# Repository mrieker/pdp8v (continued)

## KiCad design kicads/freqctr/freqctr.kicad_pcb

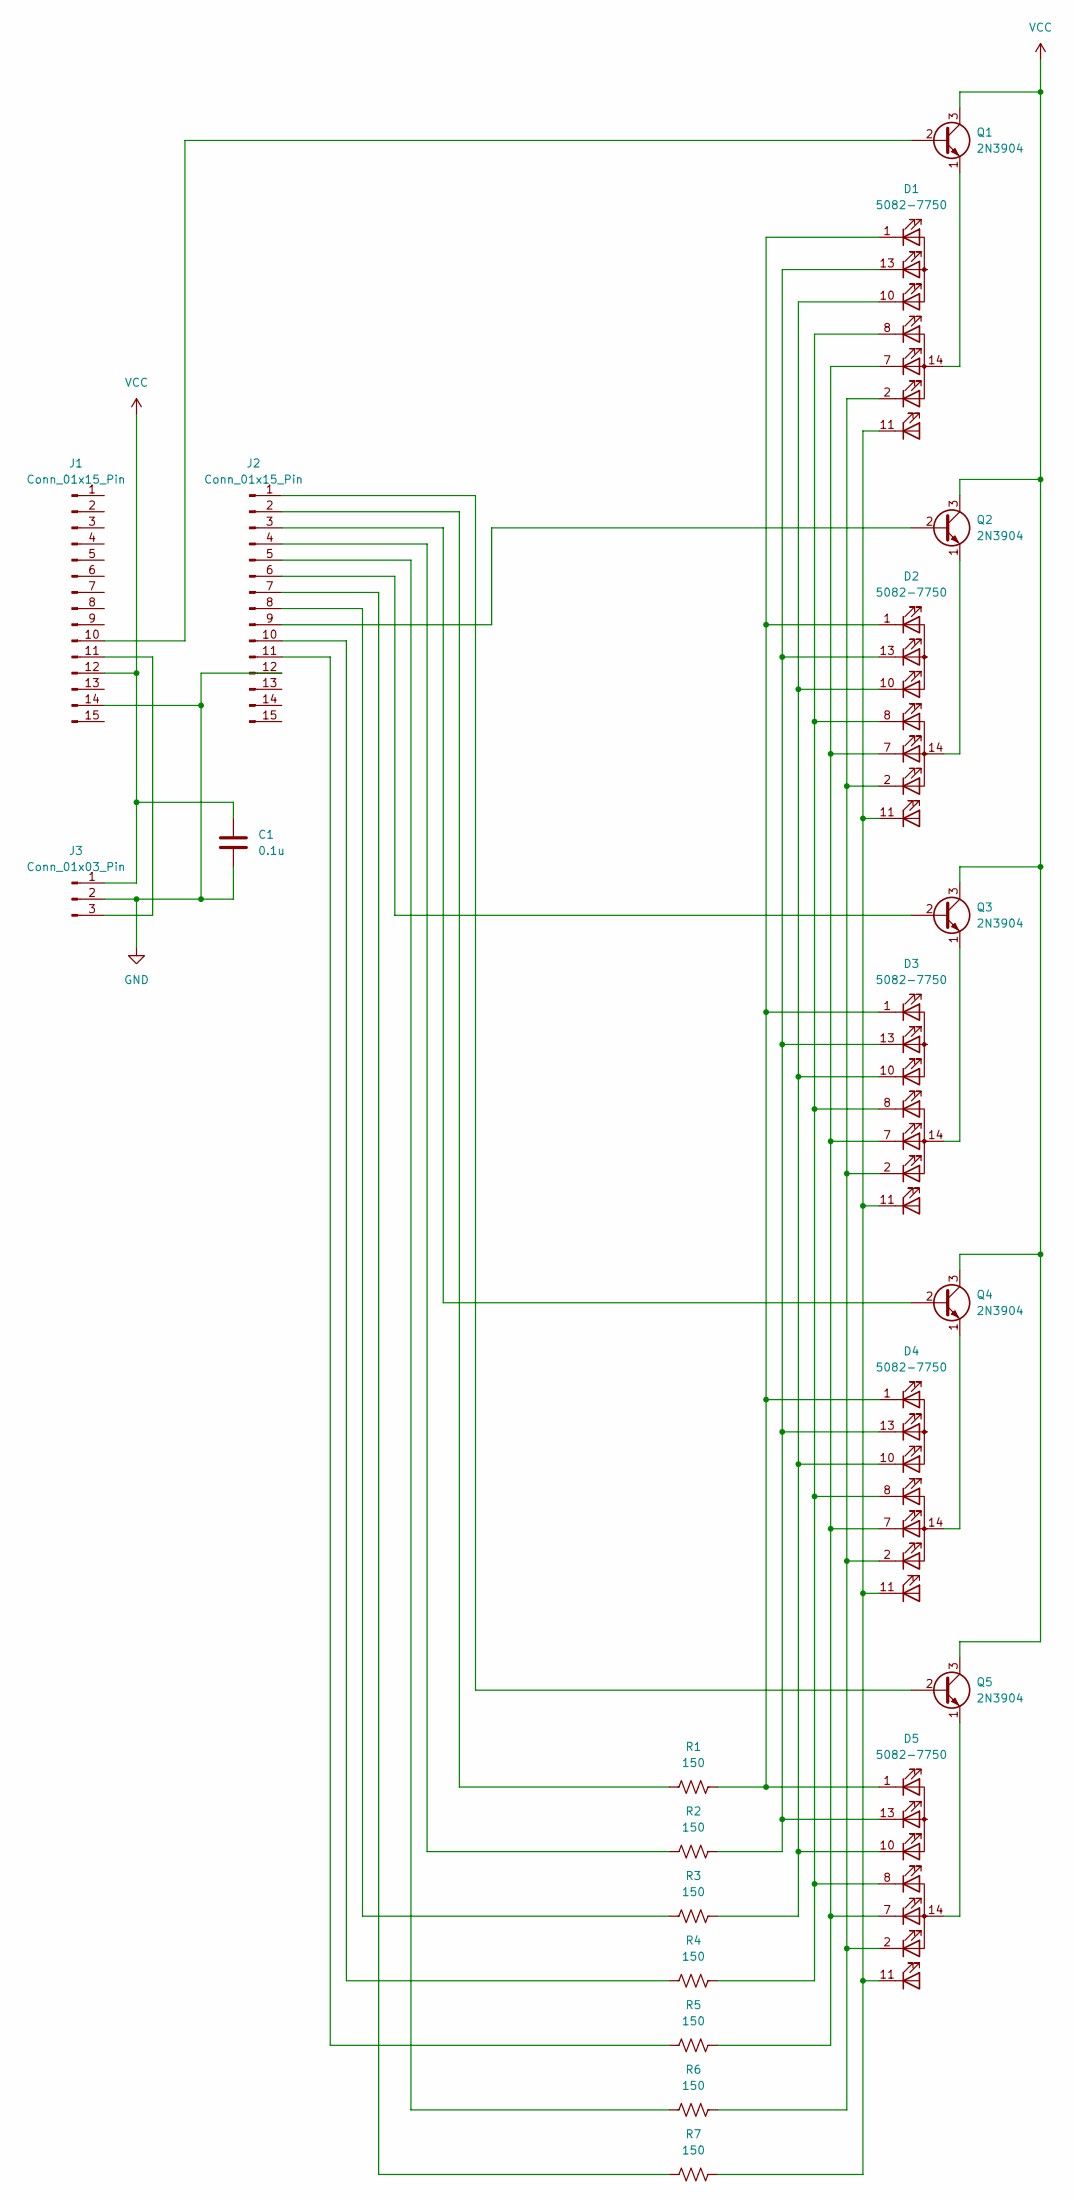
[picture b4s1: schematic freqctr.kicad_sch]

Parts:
C1: 0.1u; C_Axial_L3.8mm_D2.6mm_P7.50mm_Horizontal
D1, D2, D3, D4, D5: 5082-7750; DIP-14_W7.62mm
J1, J2: Conn_01x15_Pin; PinHeader_1x15_P2.54mm_Vertical
J3: Conn_01x03_Pin; PinHeader_1x03_P2.54mm_Vertical
Q1, Q2, Q3, Q4, Q5: 2N3904; TO-92_Inline_Wide
R1, R2, R3, R4, R5, R6, R7: 150; R_Axial_DIN0207_L6.3mm_D2.5mm_P5.08mm_Vertical

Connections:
GND: C1.2, J1.14, J2.12, J3.2
unnamed: D1.1 (a), D2.1 (a), D3.1 (a), D4.1 (a), D5.1 (a), R1.1
unnamed: D1.13 (b), D2.13 (b), D3.13 (b), D4.13 (b), D5.13 (b), R2.1
unnamed: D1.10 (c), D2.10 (c), D3.10 (c), D4.10 (c), D5.10 (c), R3.1
unnamed: D1.8 (d), D2.8 (d), D3.8 (d), D4.8 (d), D5.8 (d), R4.1
unnamed: D1.7 (e), D2.7 (e), D3.7 (e), D4.7 (e), D5.7 (e), R5.1
unnamed: D1.2 (f), D2.2 (f), D3.2 (f), D4.2 (f), D5.2 (f), R6.1
unnamed: D1.11 (g), D2.11 (g), D3.11 (g), D4.11 (g), D5.11 (g), R7.1
unnamed: D1.14 (x), Q1.1 (E)
unnamed: D2.14 (x), Q2.1 (E)
unnamed: D3.14 (x), Q3.1 (E)
unnamed: D4.14 (x), Q4.1 (E)
unnamed: D5.14 (x), Q5.1 (E)
unnamed: J1.10, Q1.2 (B)
unnamed: J1.11, J3.3
unnamed: J2.1, Q5.2 (B)
unnamed: J2.2, R1.2
unnamed: J2.3, Q4.2 (B)
unnamed: J2.4, R2.2
unnamed: J2.5, R6.2
unnamed: J2.6, Q3.2 (B)
unnamed: J2.7, R7.2
unnamed: J2.8, R3.2
unnamed: J2.9, Q2.2 (B)
unnamed: J2.10, R4.2
unnamed: J2.11, R5.2
VCC: C1.1, J1.12, J3.1, Q1.3 (C), Q2.3 (C), Q3.3 (C), Q4.3 (C), Q5.3 (C)

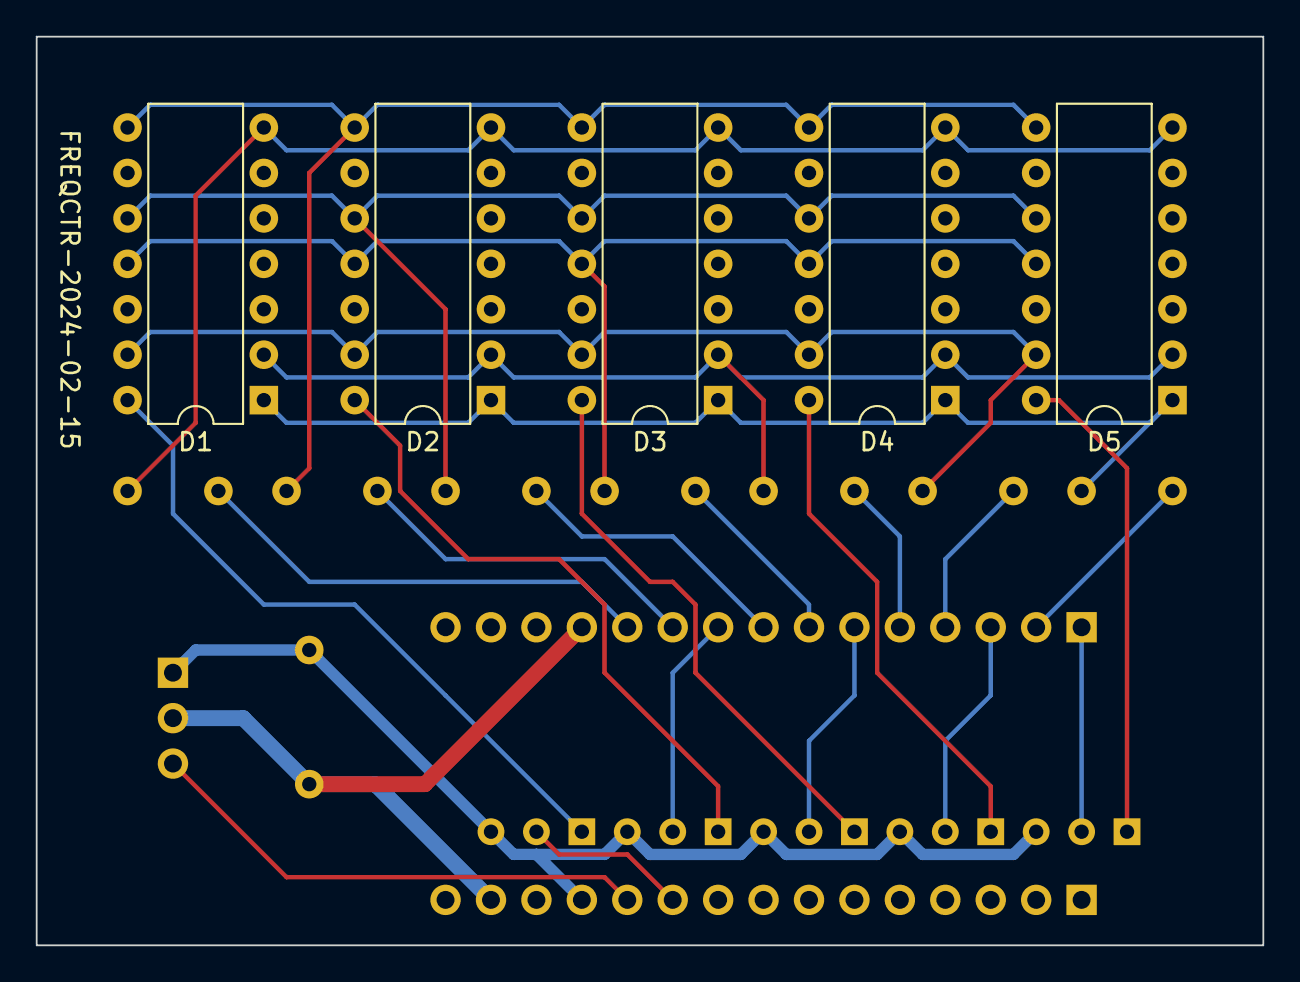
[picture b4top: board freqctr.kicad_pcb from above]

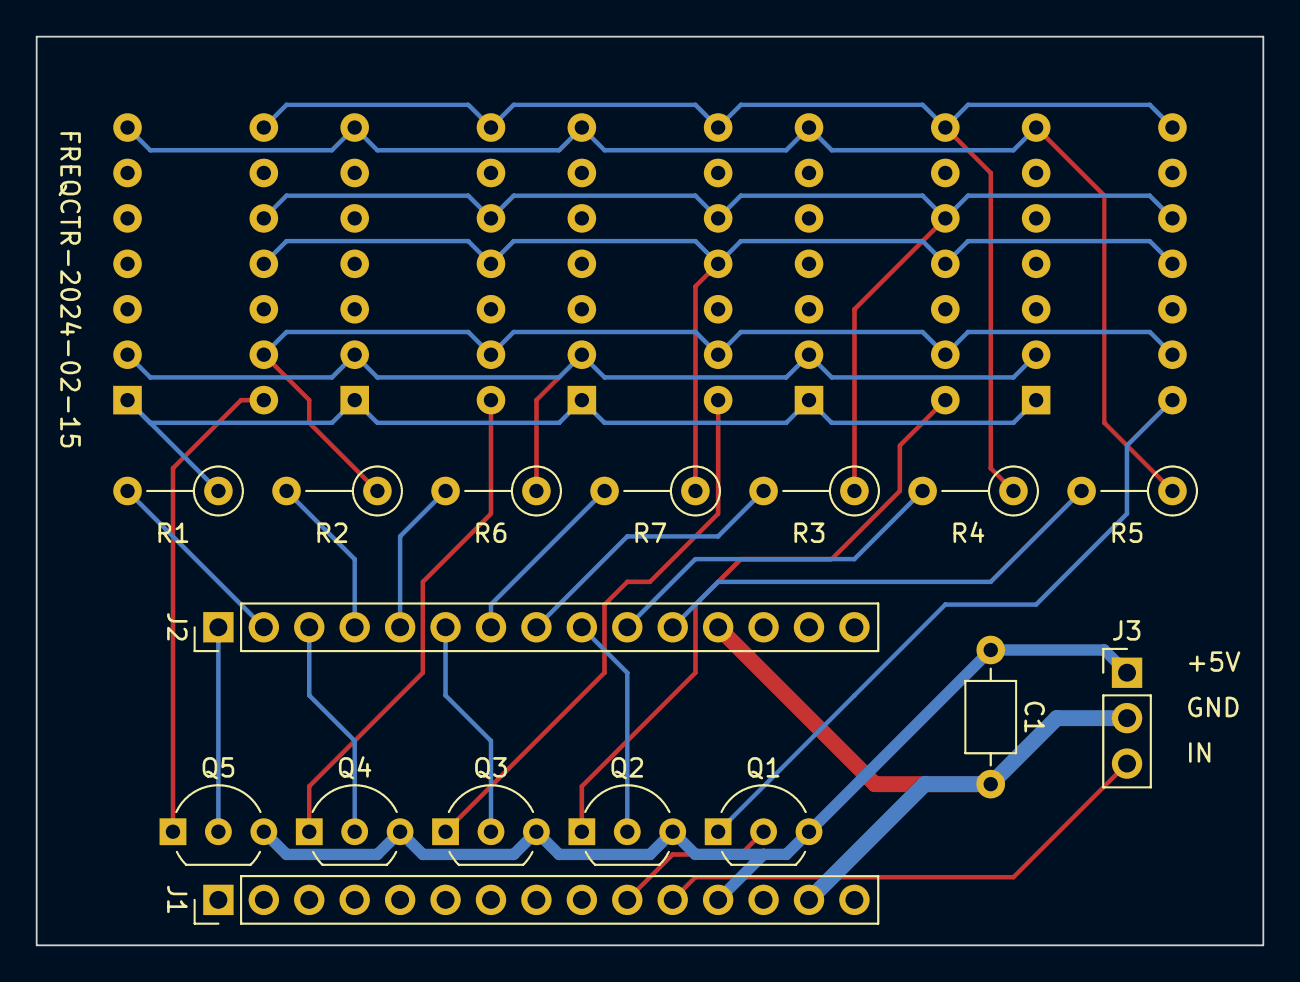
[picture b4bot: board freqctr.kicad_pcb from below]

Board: 2 copper layers, 68.6 x 50.8 mm, 21 parts (16 on the bottom side), 27 nets.

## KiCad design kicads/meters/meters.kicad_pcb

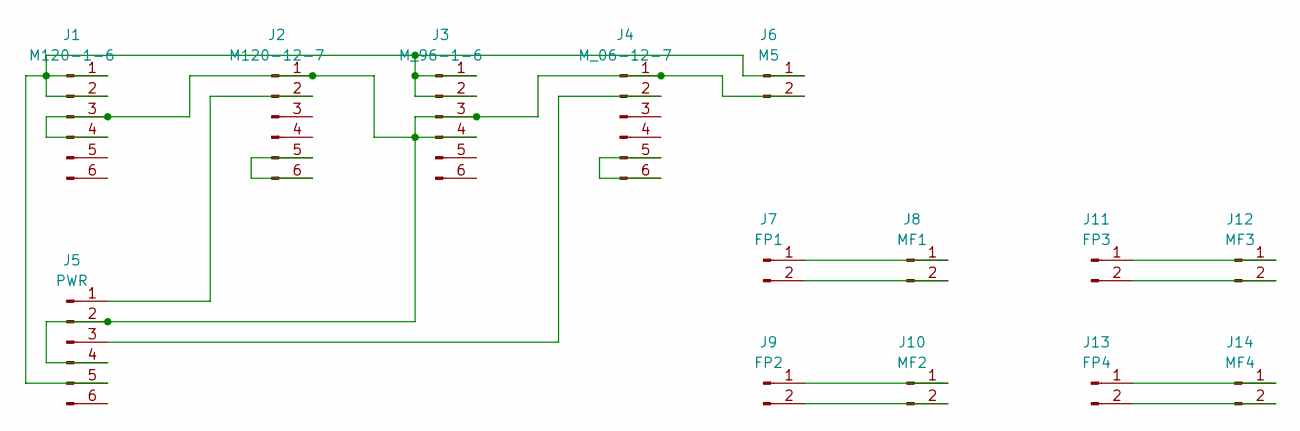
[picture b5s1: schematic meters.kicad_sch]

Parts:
J1: M120-1-6; PinSocket_1x06_P2.54mm_Vertical
J2: M120-12-7; PinSocket_1x06_P2.54mm_Vertical
J3: M_96-1-6; PinSocket_1x06_P2.54mm_Vertical
J4: M_06-12-7; PinSocket_1x06_P2.54mm_Vertical
J5: PWR; PinSocket_1x06_P2.54mm_Vertical
J6: M5; PinSocket_1x02_P2.54mm_Vertical
J7: FP1; PinSocket_1x02_P2.54mm_Vertical
J8: MF1; PinSocket_1x02_P2.54mm_Vertical
J9: FP2; PinSocket_1x02_P2.54mm_Vertical
J10: MF2; PinSocket_1x02_P2.54mm_Vertical
J11: FP3; PinSocket_1x02_P2.54mm_Vertical
J12: MF3; PinSocket_1x02_P2.54mm_Vertical
J13: FP4; PinSocket_1x02_P2.54mm_Vertical
J14: MF4; PinSocket_1x02_P2.54mm_Vertical

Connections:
unnamed: J1.1, J1.2, J3.1, J3.2, J5.5, J6.1
unnamed: J1.3, J1.4, J2.1, J3.3, J3.4, J4.1, J5.2, J5.4, J6.2
unnamed: J2.2, J5.1
unnamed: J2.5, J2.6
unnamed: J4.2, J5.3
unnamed: J4.5, J4.6
unnamed: J7.1, J8.1
unnamed: J7.2, J8.2
unnamed: J9.1, J10.1
unnamed: J9.2, J10.2
unnamed: J11.1, J12.1
unnamed: J11.2, J12.2
unnamed: J13.1, J14.1
unnamed: J13.2, J14.2

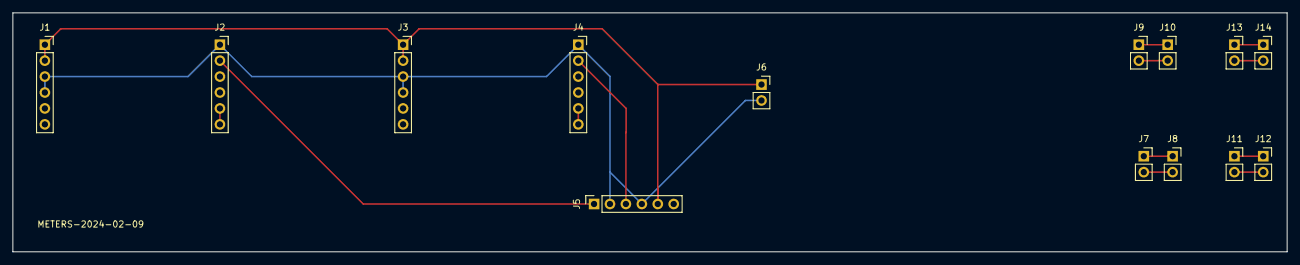
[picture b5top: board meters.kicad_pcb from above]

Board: 2 copper layers, 203.2 x 38.1 mm, 14 parts (0 on the bottom side), 14 nets.

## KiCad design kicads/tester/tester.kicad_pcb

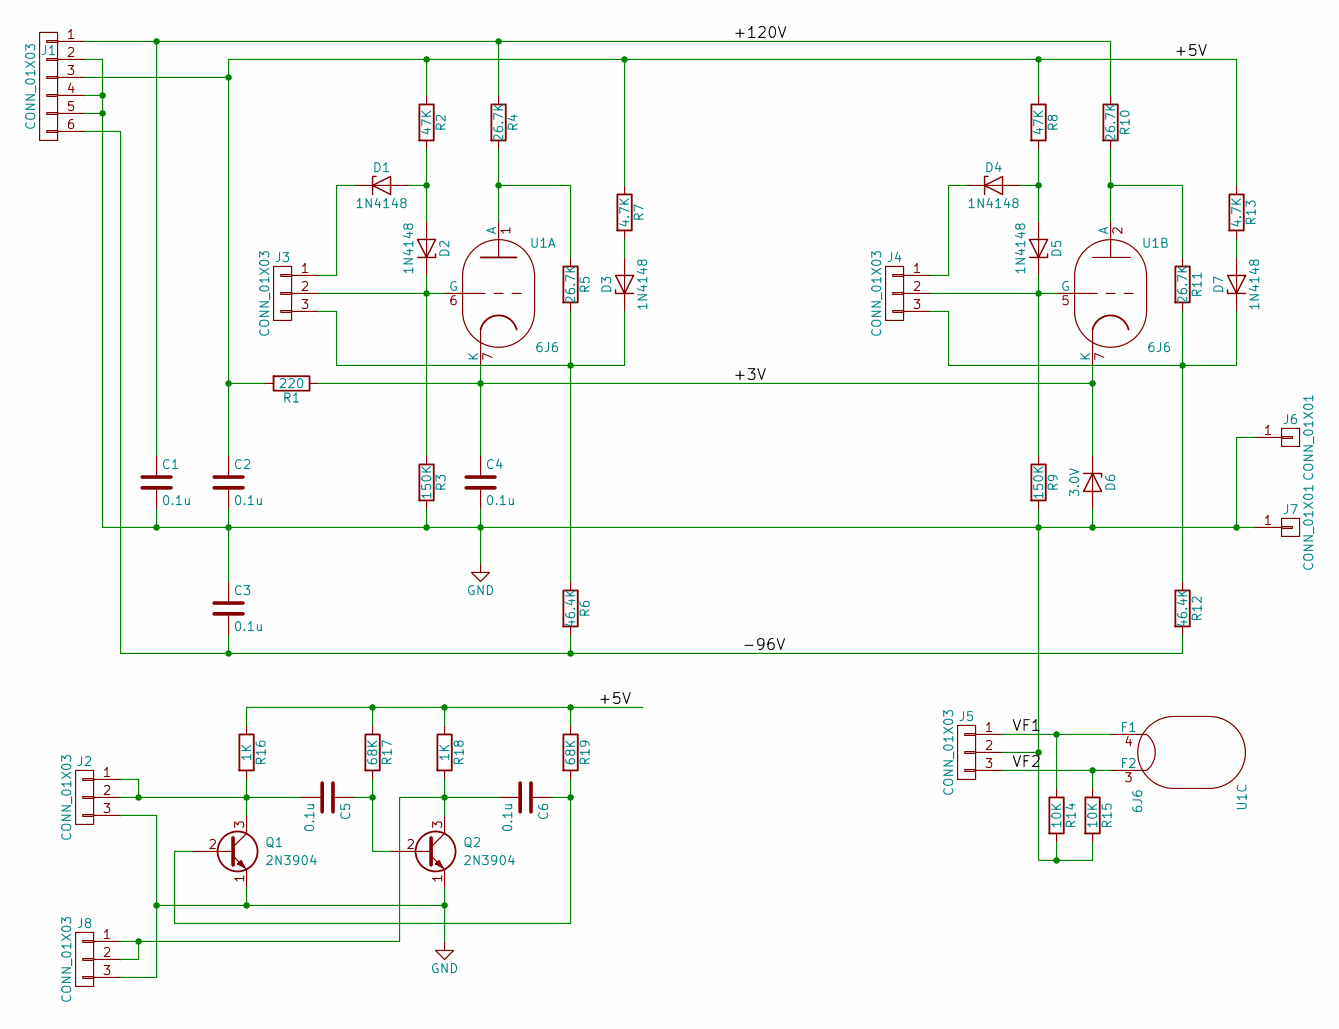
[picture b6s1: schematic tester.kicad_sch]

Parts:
C1, C2, C3, C4, C5, C6: 0.1u; C_Axial_0.1uF
D1, D2, D3, D4, D5, D7: 1N4148; D_DO-35_SOD27_P7.62mm_Horizontal
D6: 3.0V; D_DO-35_SOD27_P7.62mm_Horizontal
J1: CONN_01X03; Pin_Header_Straight_1x06_Pitch2.54mm
J2, J3, J4, J5, J8: CONN_01X03; Pin_Header_Straight_1x03_Pitch2.54mm
J6, J7: CONN_01X01; Pin_Header_Straight_1x01_Pitch2.54mm
Q1, Q2: 2N3904; TO-92_Molded_Wide
R1: 220; R_Axial_QtrWatt
R2, R8: 47K; R_Axial_QtrWatt
R3, R9: 150K; R_Axial_QtrWatt
R4, R5, R10, R11: 26.7K; R_Axial_QtrWatt
R6, R12: 46.4K; R_Axial_QtrWatt
R7, R13: 4.7K; R_Axial_QtrWatt
R14, R15: 10K; R_Axial_QtrWatt
R16, R18: 1K; R_Axial_QtrWatt
R17, R19: 68K; R_Axial_QtrWatt
U1: 6J6; B7G-0.7dia

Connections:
/+3V: C4.1, D6.1 (K), R1.1, U1.7 (K)
/+5V: C2.1, J1.3, R1.2, R2.1, R7.1, R8.1, R13.1, R16.1, R17.1, R18.1, R19.1
/+120V: C1.1, J1.1, R4.1, R10.1
/-96V: C3.2, J1.6, R6.2, R12.2
/VF1: J5.1, R14.1, U1.4 (F1)
/VF2: J5.3, R15.1, U1.3 (F2)
unnamed: C5.1, Q2.2 (B), R17.2
unnamed: C5.2, J2.1, J2.2, Q1.3 (C), R16.2
unnamed: C6.1, Q1.2 (B), R19.2
unnamed: C6.2, J8.1, J8.2, Q2.3 (C), R18.2
unnamed: D1.1 (K), J3.1
unnamed: D1.2 (A), D2.2 (A), R2.2
unnamed: D2.1 (K), J3.2, R3.1, U1.6 (G)
unnamed: D3.1 (K), J3.3, R5.2, R6.1
unnamed: D3.2 (A), R7.2
unnamed: D4.1 (K), J4.1
unnamed: D4.2 (A), D5.2 (A), R8.2
unnamed: D5.1 (K), J4.2, R9.1, U1.5 (G)
unnamed: D7.1 (K), J4.3, R11.2, R12.1
unnamed: D7.2 (A), R13.2
unnamed: R4.2, R5.1, U1.1 (A)
unnamed: R10.2, R11.1, U1.2 (A)

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
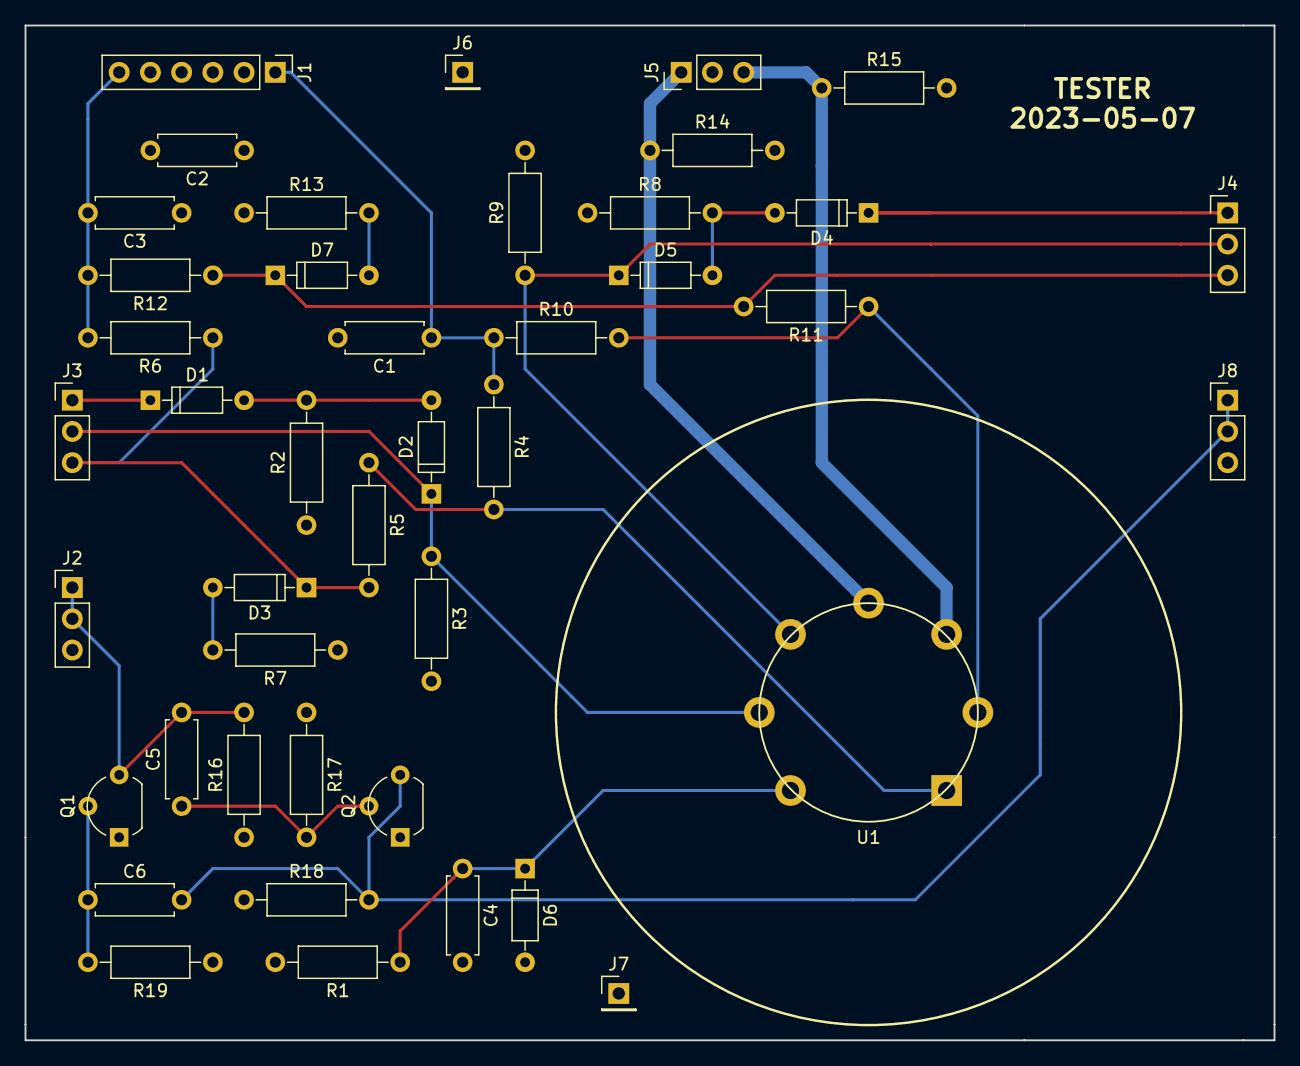
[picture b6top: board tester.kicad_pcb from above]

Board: 4 copper layers, 101.6 x 82.5 mm, 43 parts (0 on the bottom side), 23 nets.

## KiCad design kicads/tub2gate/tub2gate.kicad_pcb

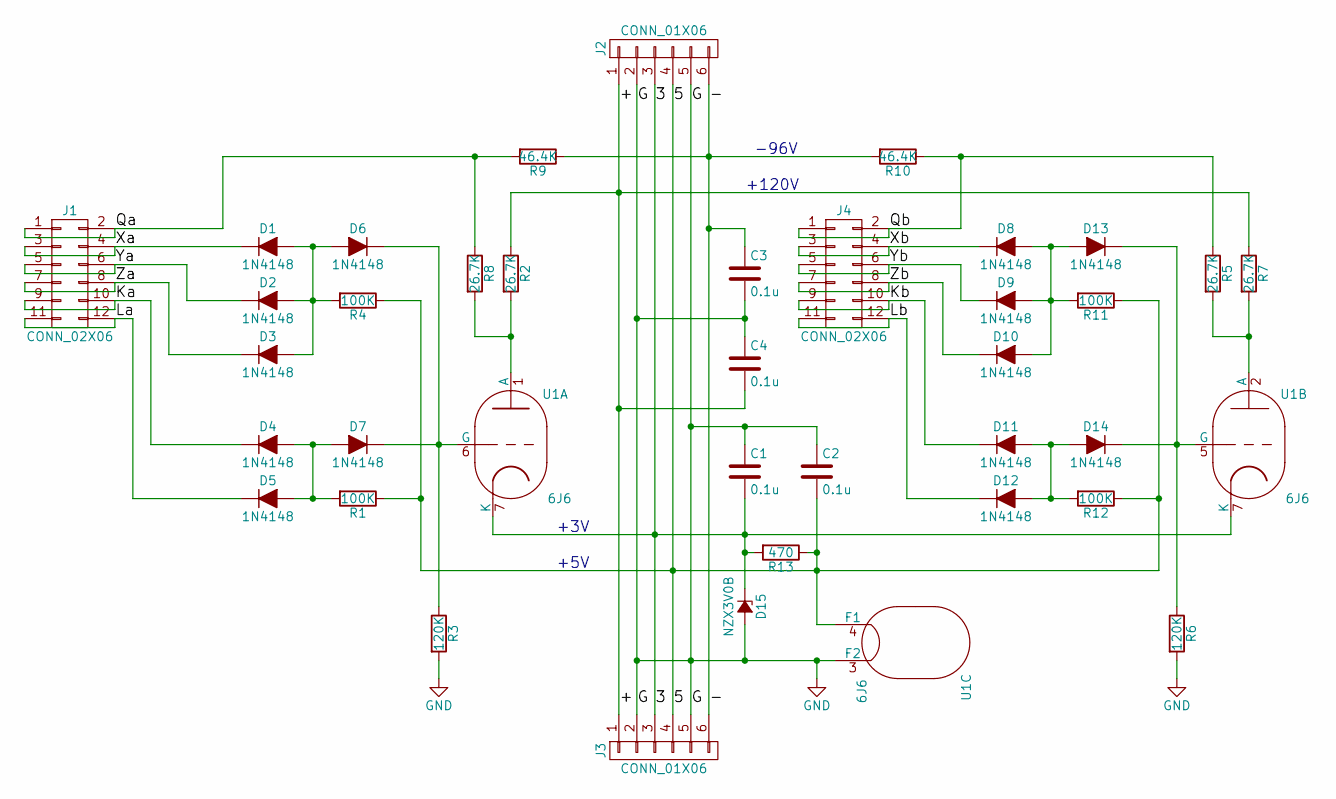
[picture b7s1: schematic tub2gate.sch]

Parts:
C1, C2, C3, C4: 0.1u; R_Axial_DIN0204_L3.6mm_D1.6mm_P7.62mm_Horizontal
D1, D2, D3, D4, D5, D6, D7, D8, D9, D10, D11, D12, D13, D14: 1N4148; D_DO-35_SOD27_P7.62mm_Horizontal
D15: NZX3V0B; D_DO-35_SOD27_P7.62mm_Horizontal
J1, J4: CONN_02X06; Pin_Header_Straight_2x06_Pitch2.54mm
J2, J3: CONN_01X06; Pin_Header_Straight_1x06_Pitch2.54mm
R1, R4, R11, R12: 100K; R_Axial_DIN0207_L6.3mm_D2.5mm_P10.16mm_Horizontal
R2, R5, R7, R8: 26.7K; R_Axial_DIN0207_L6.3mm_D2.5mm_P10.16mm_Horizontal
R3, R6: 120K; R_Axial_DIN0207_L6.3mm_D2.5mm_P10.16mm_Horizontal
R9, R10: 46.4K; R_Axial_DIN0207_L6.3mm_D2.5mm_P10.16mm_Horizontal
R13: 470; R_Axial_DIN0207_L6.3mm_D2.5mm_P10.16mm_Horizontal
U1: 6J6; B7G-0.7dia

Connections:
/3: C1.2, D15.1 (K), J2.3, J3.3, R13.2, U1.7 (K)
/5: C2.2, J2.4, J3.4, R1.1, R4.1, R11.1, R12.1, R13.1, U1.4 (F1)
/+: C4.2, J2.1, J3.1, R2.1, R7.1
/-: C3.1, J2.6, J3.6, R9.1, R10.2
/Ka: D4.1 (K), J1.9, J1.10
/Kb: D11.1 (K), J4.9, J4.10
/La: D5.1 (K), J1.11, J1.12
/Lb: D12.1 (K), J4.11, J4.12
/Qa: J1.1, J1.2, R8.1, R9.2
/Qb: J4.1, J4.2, R5.1, R10.1
/Xa: D1.1 (K), J1.3, J1.4
/Xb: D8.1 (K), J4.3, J4.4
/Ya: D2.1 (K), J1.5, J1.6
/Yb: D9.1 (K), J4.5, J4.6
/Za: D3.1 (K), J1.7, J1.8
/Zb: D10.1 (K), J4.7, J4.8
GND: C1.1, C2.1, C3.2, C4.1, D15.2 (A), J2.2, J2.5, J3.2, J3.5, R3.2, R6.2, U1.3 (F2)
unnamed: D1.2 (A), D2.2 (A), D3.2 (A), D6.2 (A), R4.2
unnamed: D4.2 (A), D5.2 (A), D7.2 (A), R1.2
unnamed: D6.1 (K), D7.1 (K), R3.1, U1.6 (G)
unnamed: D8.2 (A), D9.2 (A), D10.2 (A), D13.2 (A), R11.2
unnamed: D11.2 (A), D12.2 (A), D14.2 (A), R12.2
unnamed: D13.1 (K), D14.1 (K), R6.1, U1.5 (G)
unnamed: R2.2, R8.2, U1.1 (A)
unnamed: R5.2, R7.2, U1.2 (A)

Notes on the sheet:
-96V
+120V
+3V
+5V

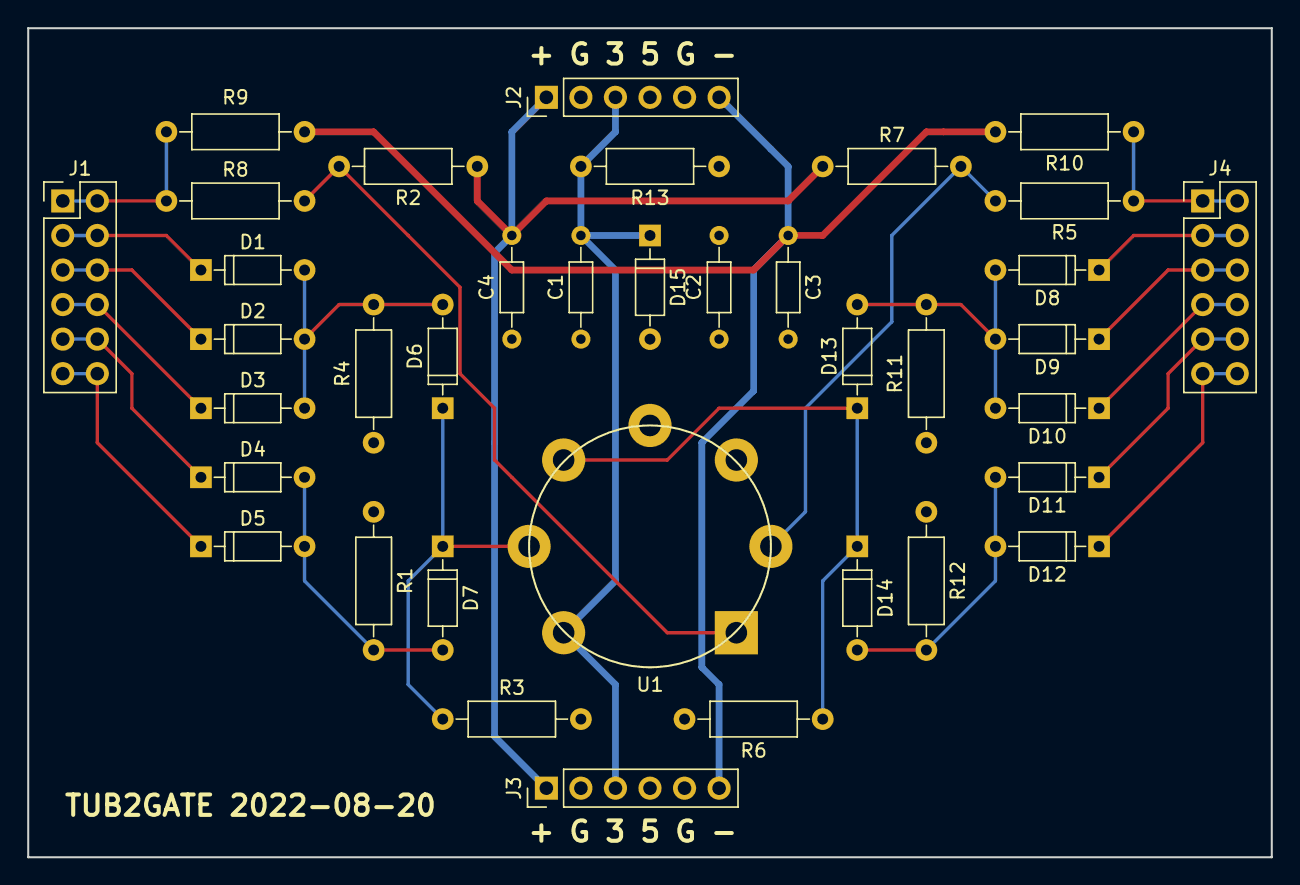
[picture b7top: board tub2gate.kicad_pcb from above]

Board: 4 copper layers, 91.4 x 61.0 mm, 37 parts (0 on the bottom side), 25 nets.
